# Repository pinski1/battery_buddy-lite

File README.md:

# battery_buddy-lite
An interface board for VW GTE 12s battery packs.

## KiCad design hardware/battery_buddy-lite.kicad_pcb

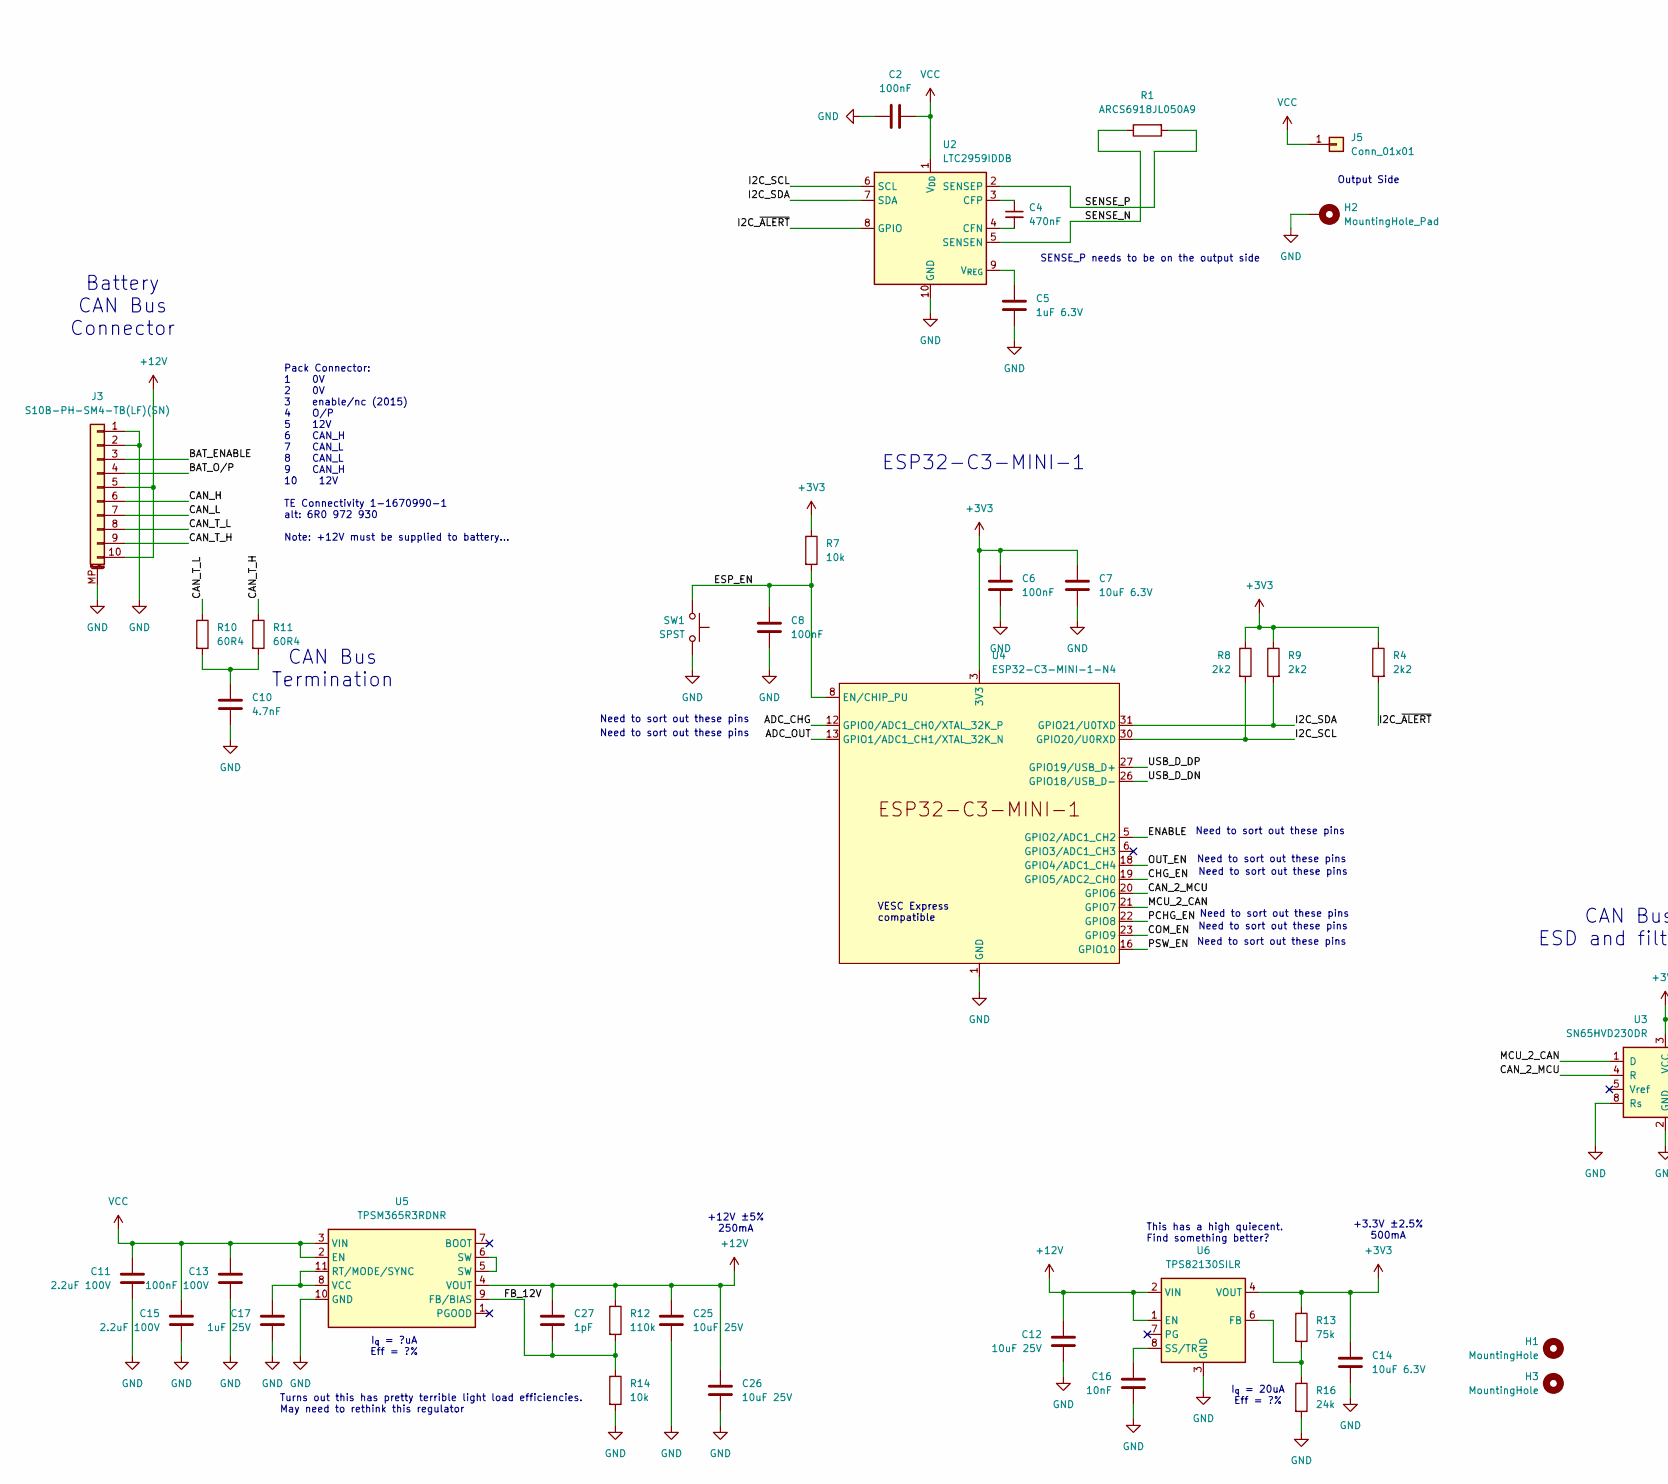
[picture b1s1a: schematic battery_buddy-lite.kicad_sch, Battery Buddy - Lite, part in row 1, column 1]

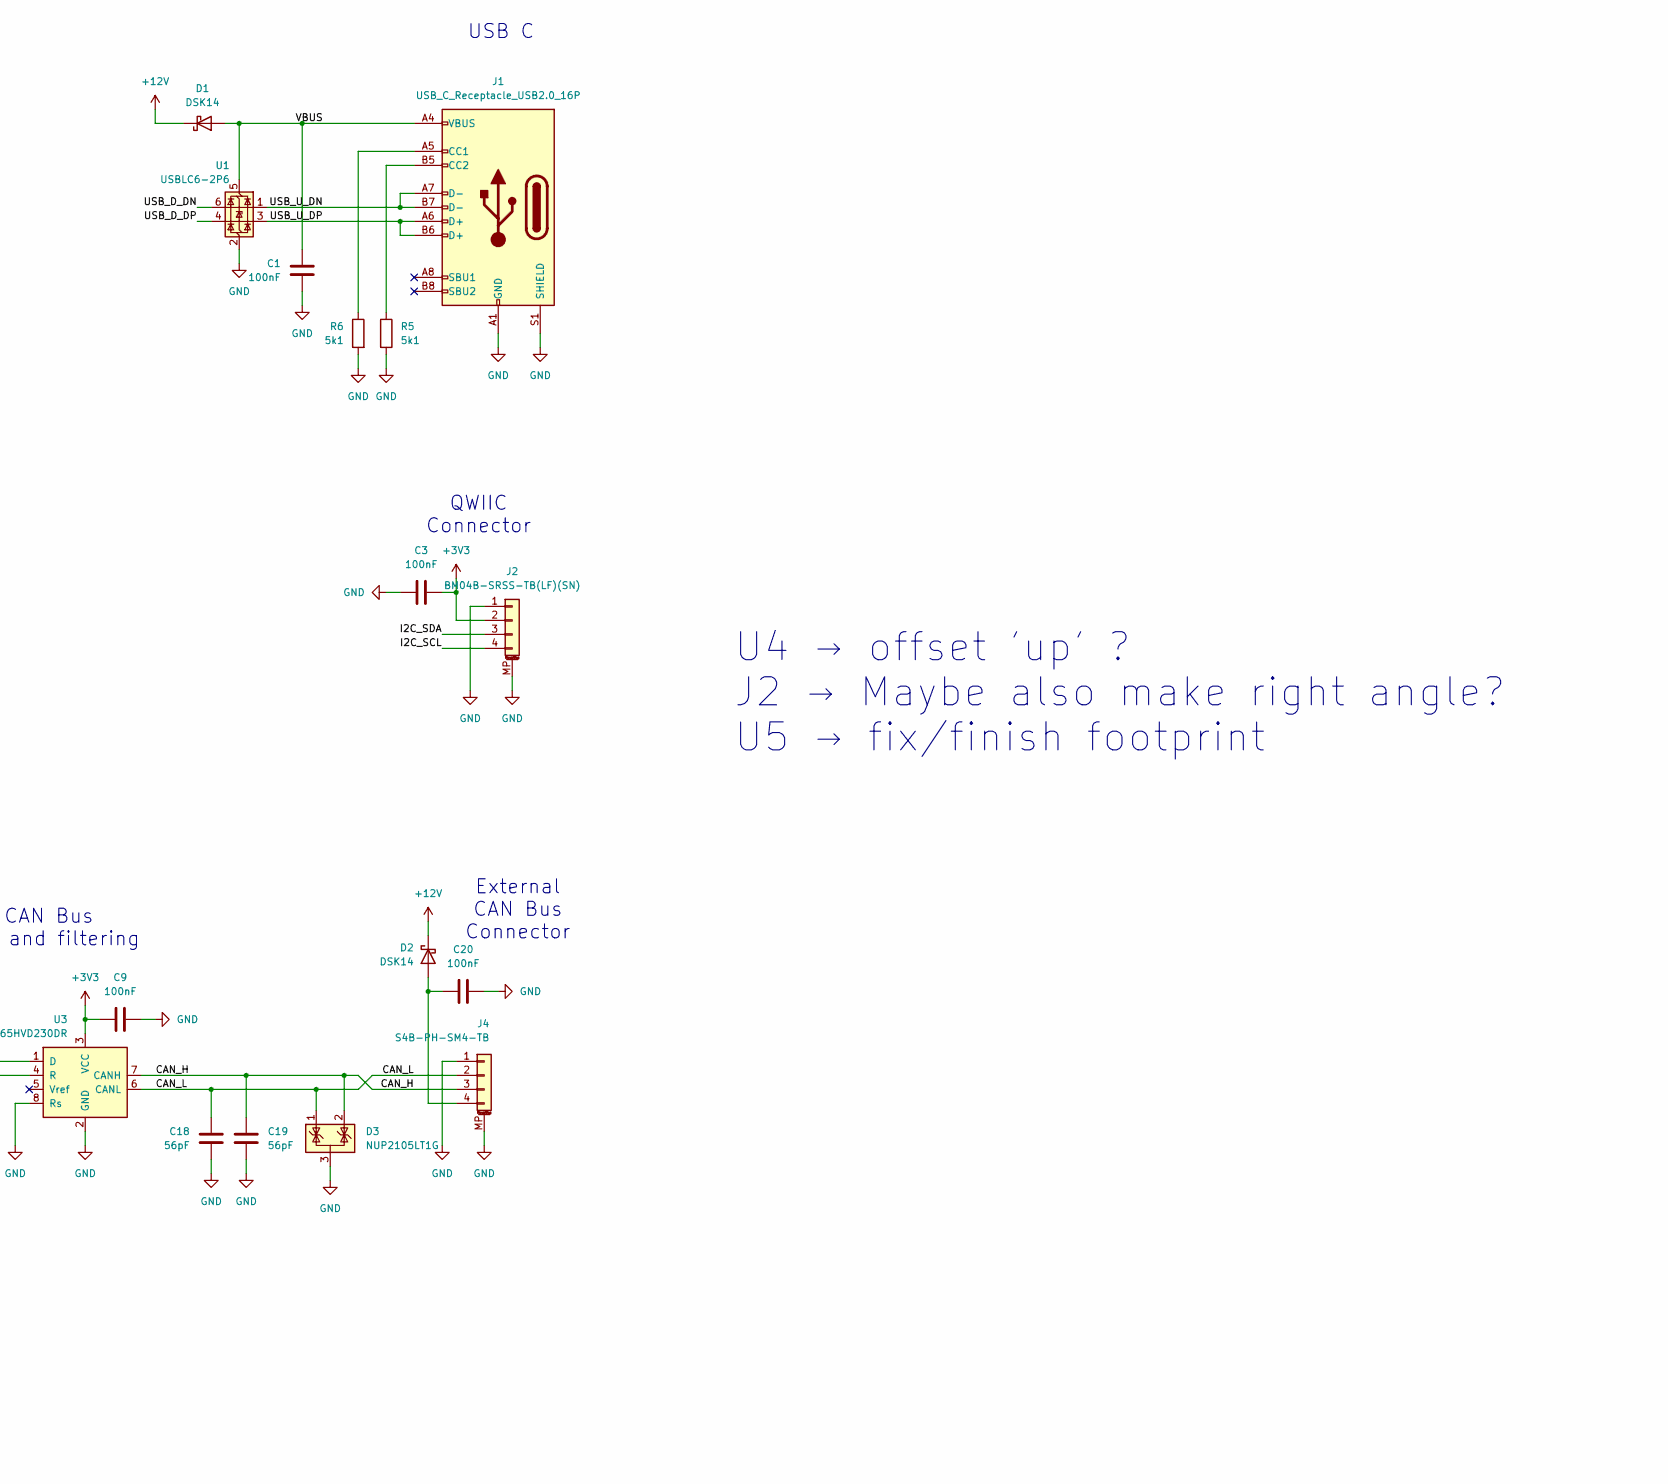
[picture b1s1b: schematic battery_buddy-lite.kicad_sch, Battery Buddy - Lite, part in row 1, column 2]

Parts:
C1, C2, C3, C6, C8, C9, C20: 100nF; C_0402_1005Metric; LCSC C1525
C4: 470nF; C_0402_1005Metric; LCSC C47339
C5: 1uF 6.3V; C_0402_1005Metric; LCSC C52923
C7, C14: 10uF 6.3V; C_0603_1608Metric; LCSC C19702
C10: 4.7nF; C_0603_1608Metric; LCSC C53987
C11, C15: 2.2uF 100V; C_1210_3225Metric; LCSC C55151
C12, C25, C26: 10uF 25V; C_1206_3216Metric; LCSC C13585
C13: 100nF 100V; C_0603_1608Metric
C16: 10nF; C_0402_1005Metric
C17: 1uF 25V; C_0603_1608Metric; LCSC C15849
C18, C19: 56pF; C_0603_1608Metric; LCSC C39148
C27: 1pF; C_0402_1005Metric; LCSC C1550
D1, D2: DSK14; D_SOD-123F; LCSC C7502711
D3: NUP2105LT1G; SOT-23; LCSC C14486
H1, H3: MountingHole; MountingHole_3.2mm_M3
H2: MountingHole_Pad; MP_Wurth_WP-BUFU_7461097; LCSC C6101229
J1: USB_C_Receptacle_USB2.0_16P; USB_C_Receptacle_Palconn_UTC16-G; LCSC C393939
J2: BM04B-SRSS-TB(LF)(SN); JST_SH_BM04B-SRSS-TB_1x04-1MP_P1.00mm_Vertical; LCSC C495539
J3: S10B-PH-SM4-TB(LF)(SN); JST_PH_S10B-PH-SM4-TB_1x10-1MP_P2.00mm_Horizontal; LCSC C265014
J4: S4B-PH-SM4-TB; JST_PH_S4B-PH-SM4-TB_1x04-1MP_P2.00mm_Horizontal; LCSC C265102
J5: Conn_01x01; SolderWire-1sqmm_1x01_D1.4mm_OD2.7mm
R1: ARCS6918JL050A9; ARCS6918FLxxxA9; LCSC C2979379
R4, R8, R9: 2k2; R_0402_1005Metric; LCSC C25879
R5, R6: 5k1; R_0402_1005Metric; LCSC C25905
R7, R14: 10k; R_0402_1005Metric; LCSC C25744
R10, R11: 60R4; R_0603_1608Metric; LCSC C23090
R12: 110k; R_0402_1005Metric; LCSC C25745
R13: 75k; R_0402_1005Metric; LCSC C25798
R16: 24k; R_0402_1005Metric; LCSC C25769
SW1: SPST; SW_Push_SPST_NO_Alps_SKRK; MPN TS-1088-AR02016; LCSC C720477
U1: USBLC6-2P6; SOT-666; LCSC C15999
U2: LTC2959IDDB; DFN-10-1EP_2x3mm_P0.5mm_EP0.64x2.4mm; LCSC C7459683
U3: SN65HVD230DR; SOIC-8_3.9x4.9mm_P1.27mm; LCSC C12084
U4: ESP32-C3-MINI-1-N4; ESP32-C3-MINI-1; LCSC C2838502
U5: TPSM365R3RDNR; Texas_RDN0011A_QFN-FCMOD; LCSC C20346007
U6: TPS82130SILR; Texas_SIL0008D_MicroSiP-8-1EP_2.8x3mm_P0.65mm_EP1.1x1.9mm_T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; LCSC C473914

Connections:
+3V3: C3.1, C6.1, C7.1, C9.1, C14.1, J2.2, R4.1, R7.1, R8.1, R9.1, R13.1, U3.3 (VCC), U4.3 (3V3), U6.4 (VOUT), U6.5 (VOUT)
+12V: C12.1, C25.1, C26.1, C27.1, D1.1 (K), D2.1 (K), J3.5, J3.10, R12.1, U5.4 (VOUT), U6.1 (EN), U6.2 (VIN)
/ADC_CHG: U4.12 (GPIO0/ADC1_CH0/XTAL_32K_P)
/ADC_OUT: U4.13 (GPIO1/ADC1_CH1/XTAL_32K_N)
/BAT_ENABLE: J3.3
/BAT_O/P: J3.4
/CAN_2_MCU: U3.4 (R), U4.20 (GPIO6)
/CAN_H: C19.1, D3.2 (K), J3.6, J4.3, U3.7 (CANH)
/CAN_L: C18.1, D3.1 (K), J3.7, J4.2, U3.6 (CANL)
/CAN_T_H: J3.9, R11.1
/CAN_T_L: J3.8, R10.1
/CHG_EN: U4.19 (GPIO5/ADC2_CH0)
/COM_EN: U4.23 (GPIO9)
/ENABLE: U4.5 (GPIO2/ADC1_CH2)
/ESP_EN: C8.1, R7.2, SW1.2, U4.8 (EN/CHIP_PU)
/FB_12V: C27.2, R12.2, R14.1, U5.9 (FB/BIAS)
/I2C_SCL: J2.4, R8.2, U2.6 (SCL), U4.30 (GPIO20/U0RXD)
/I2C_SDA: J2.3, R9.2, U2.7 (SDA), U4.31 (GPIO21/U0TXD)
/I2C_~ALERT: R4.2, U2.8 (GPIO)
/MCU_2_CAN: U3.1 (D), U4.21 (GPIO7)
/OUT_EN: U4.18 (GPIO4/ADC1_CH4)
/PCHG_EN: U4.22 (GPIO8)
/PSW_EN: U4.16 (GPIO10)
/SENSE_N: R1.1, U2.5 (SENSEN)
/SENSE_P: R1.2, U2.2 (SENSEP)
/USB_D_DN: U1.6 (I/O1), U4.26 (GPIO18/USB_D-)
/USB_D_DP: U1.4 (I/O2), U4.27 (GPIO19/USB_D+)
/USB_U_DN: J1.A7 (D-), J1.B7 (D-), U1.1 (I/O1)
/USB_U_DP: J1.A6 (D+), J1.B6 (D+), U1.3 (I/O2)
/VBUS: C1.2, D1.2 (A), J1.A4 (VBUS), J1.A9 (VBUS), J1.B4 (VBUS), J1.B9 (VBUS), U1.5 (VBUS)
GND: C1.1, C2.1, C3.2, C5.1, C6.2, C7.2, C8.2, C9.2, C10.2, C11.2, C12.2, C13.2, C14.2, C15.2, C16.2, C17.2, C18.2, C19.2, C20.2, C25.2, C26.2, D3.3 (A), H2.1, J1.A1 (GND), J1.A12 (GND), J1.B1 (GND), J1.B12 (GND), J1.S1 (SHIELD), J2.1, J2.MP (MountPin), J3.1, J3.2, J3.MP (MountPin), J4.1, J4.MP (MountPin), R5.2, R6.2, R14.2, R16.2, SW1.1, U1.2 (GND), U2.10 (GND), U3.2 (GND), U3.8 (Rs), U4.1 (GND), U4.2 (GND), U4.11 (GND), U4.14 (GND), U4.36 (GND), U4.37 (GND), U4.38 (GND), U4.39 (GND), U4.40 (GND), U4.41 (GND), U4.42 (GND), U4.43 (GND), U4.44 (GND), U4.45 (GND), U4.46 (GND), U4.47 (GND), U4.48 (GND), U4.49 (GND), U4.50 (GND), U4.51 (GND), U4.52 (GND), U4.53 (GND), U5.10 (GND), U6.3 (GND), U6.9 (GND)
unnamed: C10.1, R10.2, R11.2
unnamed: C20.1, D2.2 (A), J4.4
unnamed: J1.A5 (CC1), R6.1
unnamed: J1.B5 (CC2), R5.1
unnamed: C4.2, U2.4 (CFN)
unnamed: C4.1, U2.3 (CFP)
unnamed: C5.2, U2.9 (V_{REG})
unnamed: C17.1, U5.8 (VCC), U5.11 (RT/MODE/SYNC)
unnamed: U5.5 (SW), U5.6 (SW)
unnamed: R13.2, R16.1, U6.6 (FB)
unnamed: C16.1, U6.8 (SS/TR)
VCC: C2.2, C11.1, C13.1, C15.1, J5.1, U2.1 (V_{DD}), U5.2 (EN), U5.3 (VIN)

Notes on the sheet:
Battery CAN Bus Connector
Need to sort out these pins
+3.3V ±2.5% 500mA
I_{q} = ?uA Eff = ?%
Output Side
+12V ±5% 250mA
U4 → offset 'up' ? J2 → Maybe also make right angle? U5 → fix/finish footprint
USB C
External CAN Bus Connector
QWIIC Connector
SENSE_P needs to be on the output side
Pack Connector: 1 0V 2 0V 3 enable/nc (2015) 4 O/P 5 12V 6 CAN_H 7 CAN_L 8 CAN_L 9 CAN_H 10 12V TE Connectivity 1-1670990-1 alt: 6R0 972 930 Note: +12V must be supplied to battery...
ESP32-C3-MINI-1
VESC Express compatible
Turns out this has pretty terrible light load efficiencies. May need to rethink this regulator
I_{q} = 20uA Eff = ?%
This has a high quiecent. Find something better?
CAN Bus Termination
CAN Bus ESD and filtering

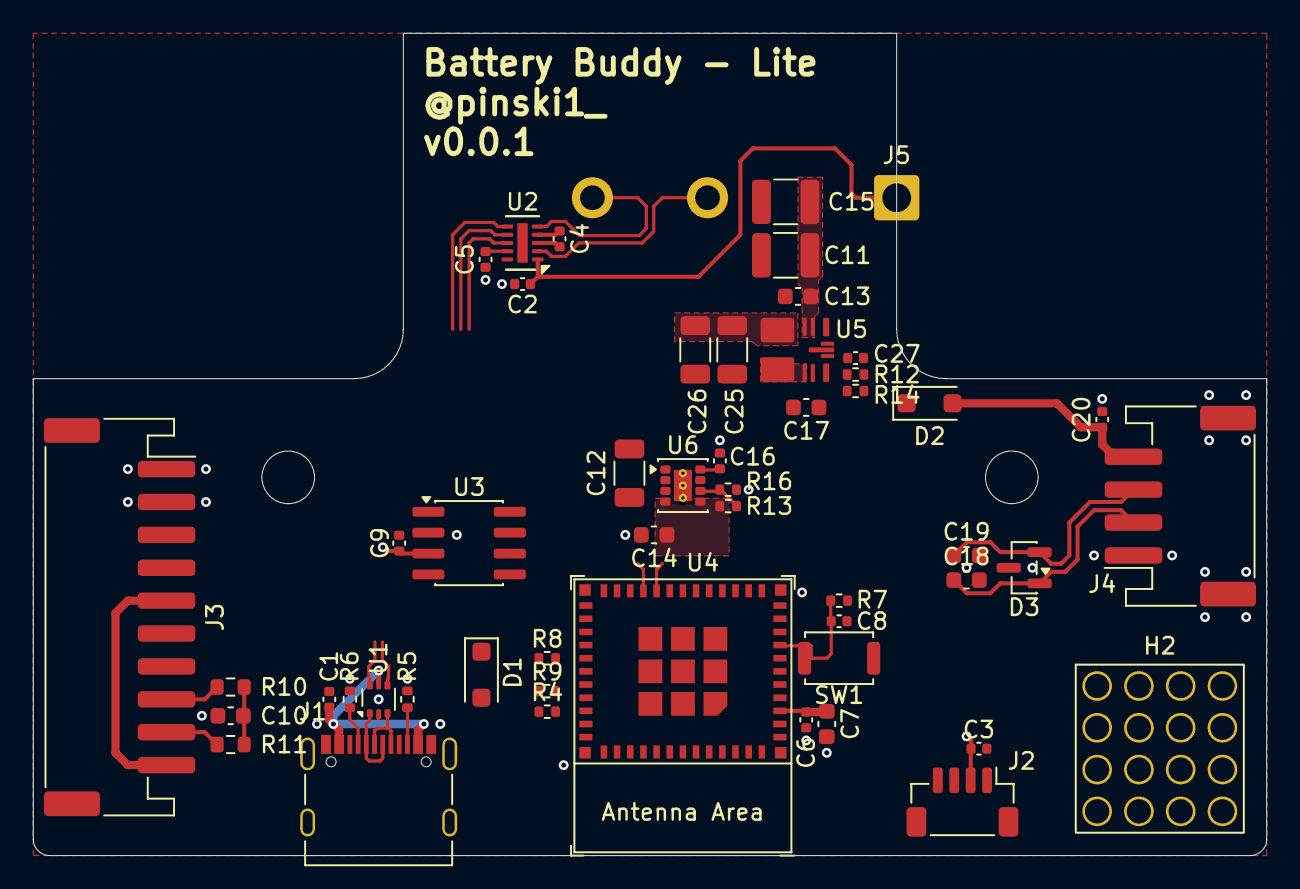
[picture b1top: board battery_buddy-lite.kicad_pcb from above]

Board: 2 copper layers, 75.0 x 50.0 mm, 54 parts (1 on the bottom side), 33 nets.

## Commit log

2026-03-02 masking pin 11 of LTC2959
2026-03-02 updating gitignore
2026-03-02 removing generated files
2026-03-02 missed a file
2026-03-02 updating board shape and USB C conn
